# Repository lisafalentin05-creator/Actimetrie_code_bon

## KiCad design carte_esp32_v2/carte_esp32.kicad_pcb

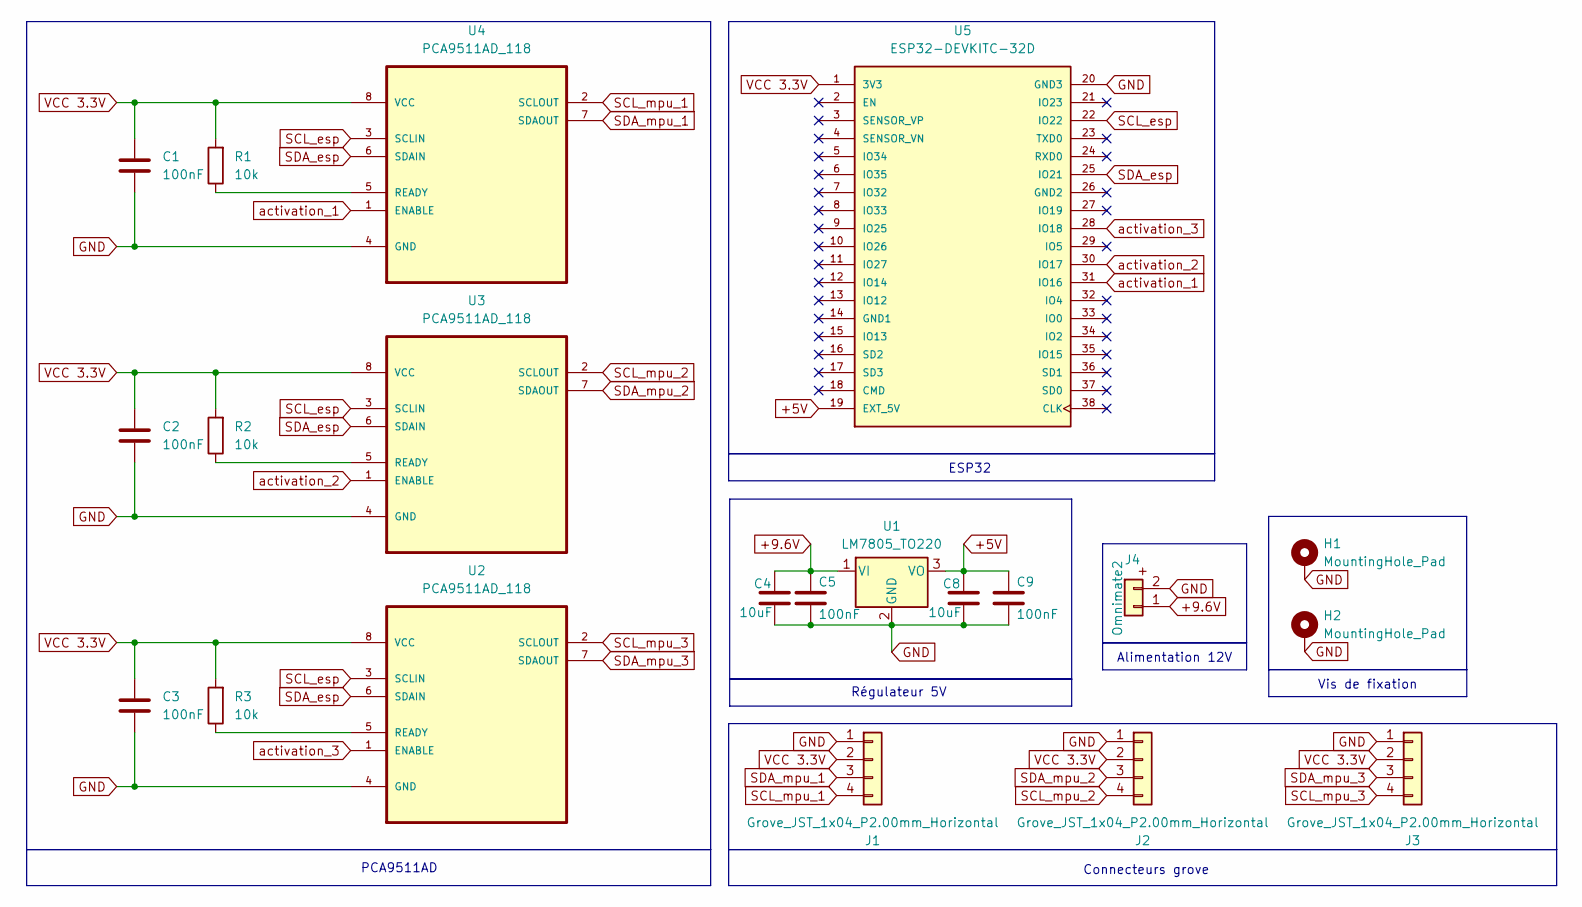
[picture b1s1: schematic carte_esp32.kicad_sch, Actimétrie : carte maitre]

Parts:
C1, C2, C3, C5, C9: 100nF; C_1206_3216Metric
C4, C8: 10uF; C_1206_3216Metric
H1, H2: MountingHole_Pad; MountingHole_3.2mm_M3_DIN965_Pad_TopBottom
J1, J2, J3: Grove_JST_1x04_P2.00mm_Horizontal; JST_PH_B4B-PH-K_1x04_P2.00mm_Vertical
J4: Omnimate2; OmnimateSL-5,08_1x02_P5.08mm_Vertical
R1, R2, R3: 10k; R_1206_3216Metric
U1: LM7805_TO220; TO-220-3_Horizontal_TabDown
U2, U3, U4: PCA9511AD_118; SOT96-1_NXP; MPN PCA9511AD,118
U5: ESP32-DEVKITC-32D; MODULE_ESP32-DEVKITC-32D

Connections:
+5V: C8.1, C9.1, U1.3 (VO), U5.19 (EXT_5V)
+9.6V: C4.1, C5.1, J4.1, U1.1 (VI)
GND: C1.2, C2.2, C3.2, C4.2, C5.2, C8.2, C9.2, H1.1, H2.1, J1.1, J2.1, J3.1, J4.2, U1.2 (GND), U2.4 (GND), U3.4 (GND), U4.4 (GND), U5.20 (GND3)
unnamed: R3.1, U2.5 (READY)
unnamed: R2.1, U3.5 (READY)
unnamed: R1.1, U4.5 (READY)
SCL_esp: U2.3 (SCLIN), U3.3 (SCLIN), U4.3 (SCLIN), U5.22 (IO22)
SCL_mpu_1: J1.4, U4.2 (SCLOUT)
SCL_mpu_2: J2.4, U3.2 (SCLOUT)
SCL_mpu_3: J3.4, U2.2 (SCLOUT)
SDA_esp: U2.6 (SDAIN), U3.6 (SDAIN), U4.6 (SDAIN), U5.25 (IO21)
SDA_mpu_1: J1.3, U4.7 (SDAOUT)
SDA_mpu_2: J2.3, U3.7 (SDAOUT)
SDA_mpu_3: J3.3, U2.7 (SDAOUT)
VCC 3.3V: C1.1, C2.1, C3.1, J1.2, J2.2, J3.2, R1.2, R2.2, R3.2, U2.8 (VCC), U3.8 (VCC), U4.8 (VCC), U5.1 (3V3)
activation_1: U4.1 (ENABLE), U5.31 (IO16)
activation_2: U3.1 (ENABLE), U5.30 (IO17)
activation_3: U2.1 (ENABLE), U5.28 (IO18)

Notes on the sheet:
Alimentation 12V
ESP32
Connecteurs grove
PCA9511AD
Régulateur 5V
Vis de fixation

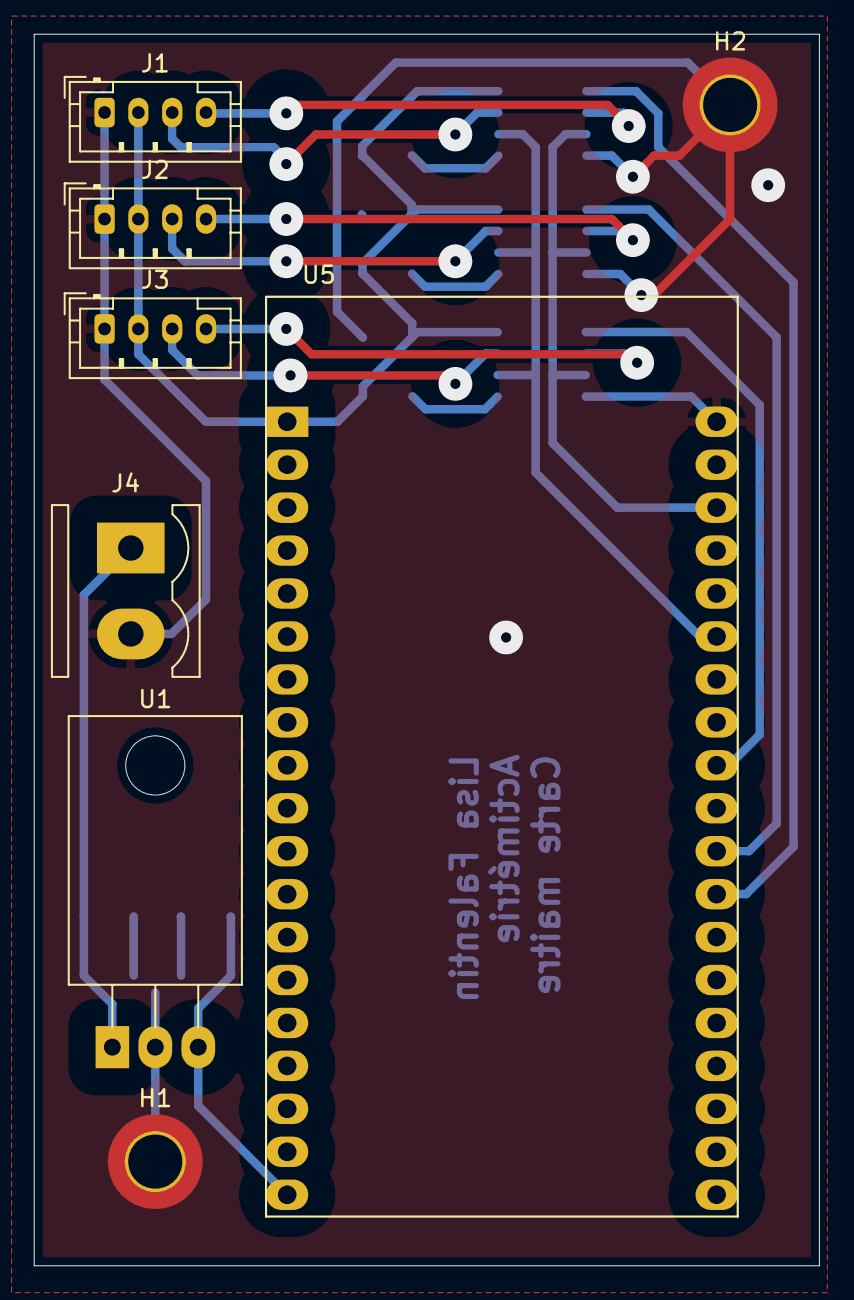
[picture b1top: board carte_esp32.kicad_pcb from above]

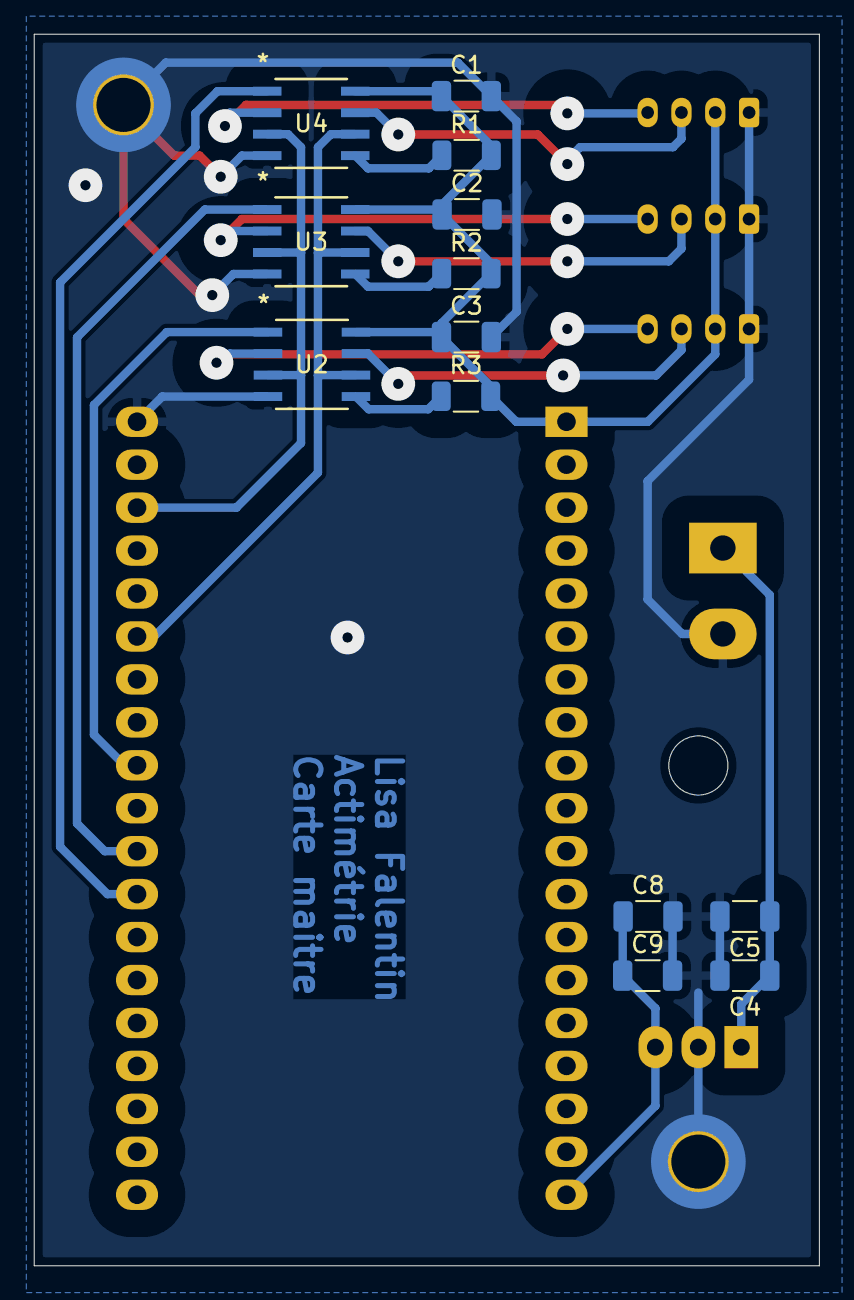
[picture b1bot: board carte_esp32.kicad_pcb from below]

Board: 2 copper layers, 46.4 x 72.8 mm, 21 parts (13 on the bottom side), 18 nets.

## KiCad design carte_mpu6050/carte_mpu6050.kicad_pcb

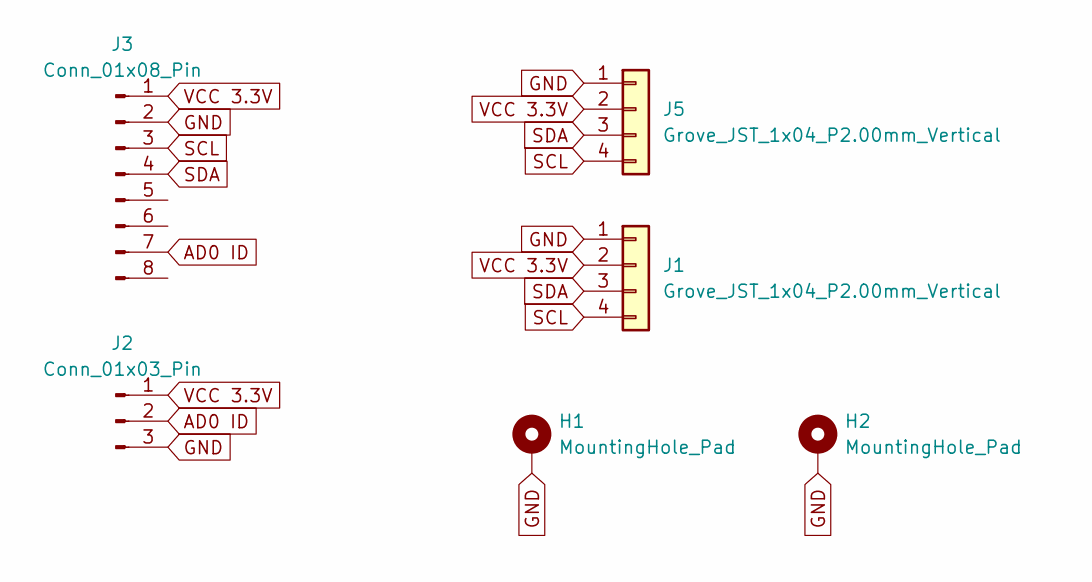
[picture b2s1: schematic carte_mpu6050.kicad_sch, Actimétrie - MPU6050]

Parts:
H1, H2: MountingHole_Pad; MountingHole_2.2mm_M2_DIN965_Pad_TopBottom
J1, J5: Grove_JST_1x04_P2.00mm_Vertical; JST_PH_B4B-PH-K_1x04_P2.00mm_Vertical
J2: Conn_01x03_Pin; PinHeader_1x03_P2.54mm_Vertical
J3: Conn_01x08_Pin; PinSocket_1x08_P2.54mm_Horizontal

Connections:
AD0 ID: J2.2, J3.7
GND: H1.1, H2.1, J1.1, J2.3, J3.2, J5.1
SCL: J1.4, J3.3, J5.4
SDA: J1.3, J3.4, J5.3
VCC 3.3V: J1.2, J2.1, J3.1, J5.2

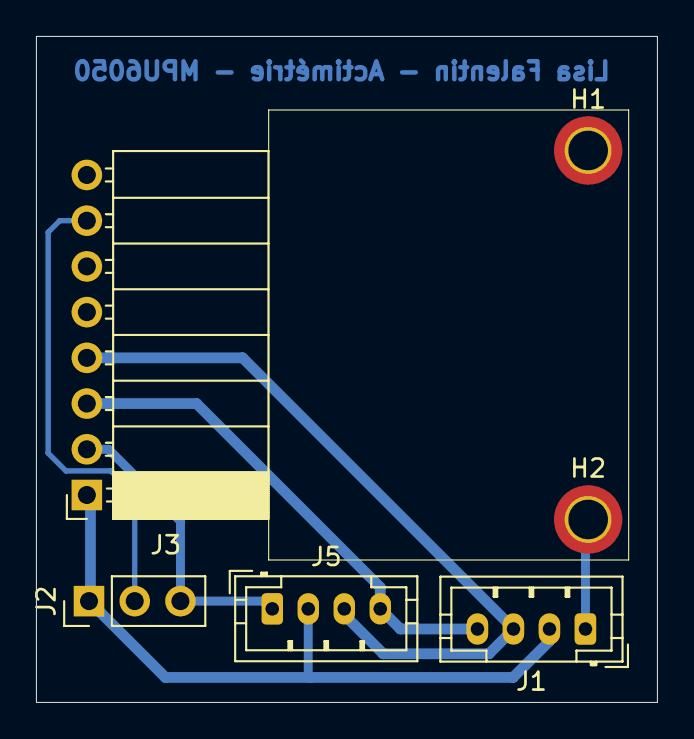
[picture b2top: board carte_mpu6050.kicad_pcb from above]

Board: 2 copper layers, 34.5 x 37.0 mm, 6 parts (0 on the bottom side), 5 nets.

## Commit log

2026-06-17 modif pour enlever la dérive après l'init lorsque bonhomme immobile
2026-06-19 ajout android 3 fragments, fragment 3 en cours, seulement bras gauche et bras droit valides
2026-06-22 posture 2d pivotable sur elle-même
2026-06-22 flexion correcte bras gauche
2026-06-22 ajout kicad des cartes elec esp + mpu
2026-06-22 travail sur le bras droit : position des capteurs différente position visuelle
2026-06-23 ajustement des visuels des bras avec des limites pour garder un visuel propre
2026-06-23 ajout vérif détection des capteurs daqns le terminal
2026-06-23 tjs pb tête et visuel
2026-06-24 mouvements tete et nuque fragment 3 stoppés
2026-06-24 ajout du beta pour meilleur réactivité
2026-06-24 version avec membres ok
2026-06-24 ajout du projet solidworks
